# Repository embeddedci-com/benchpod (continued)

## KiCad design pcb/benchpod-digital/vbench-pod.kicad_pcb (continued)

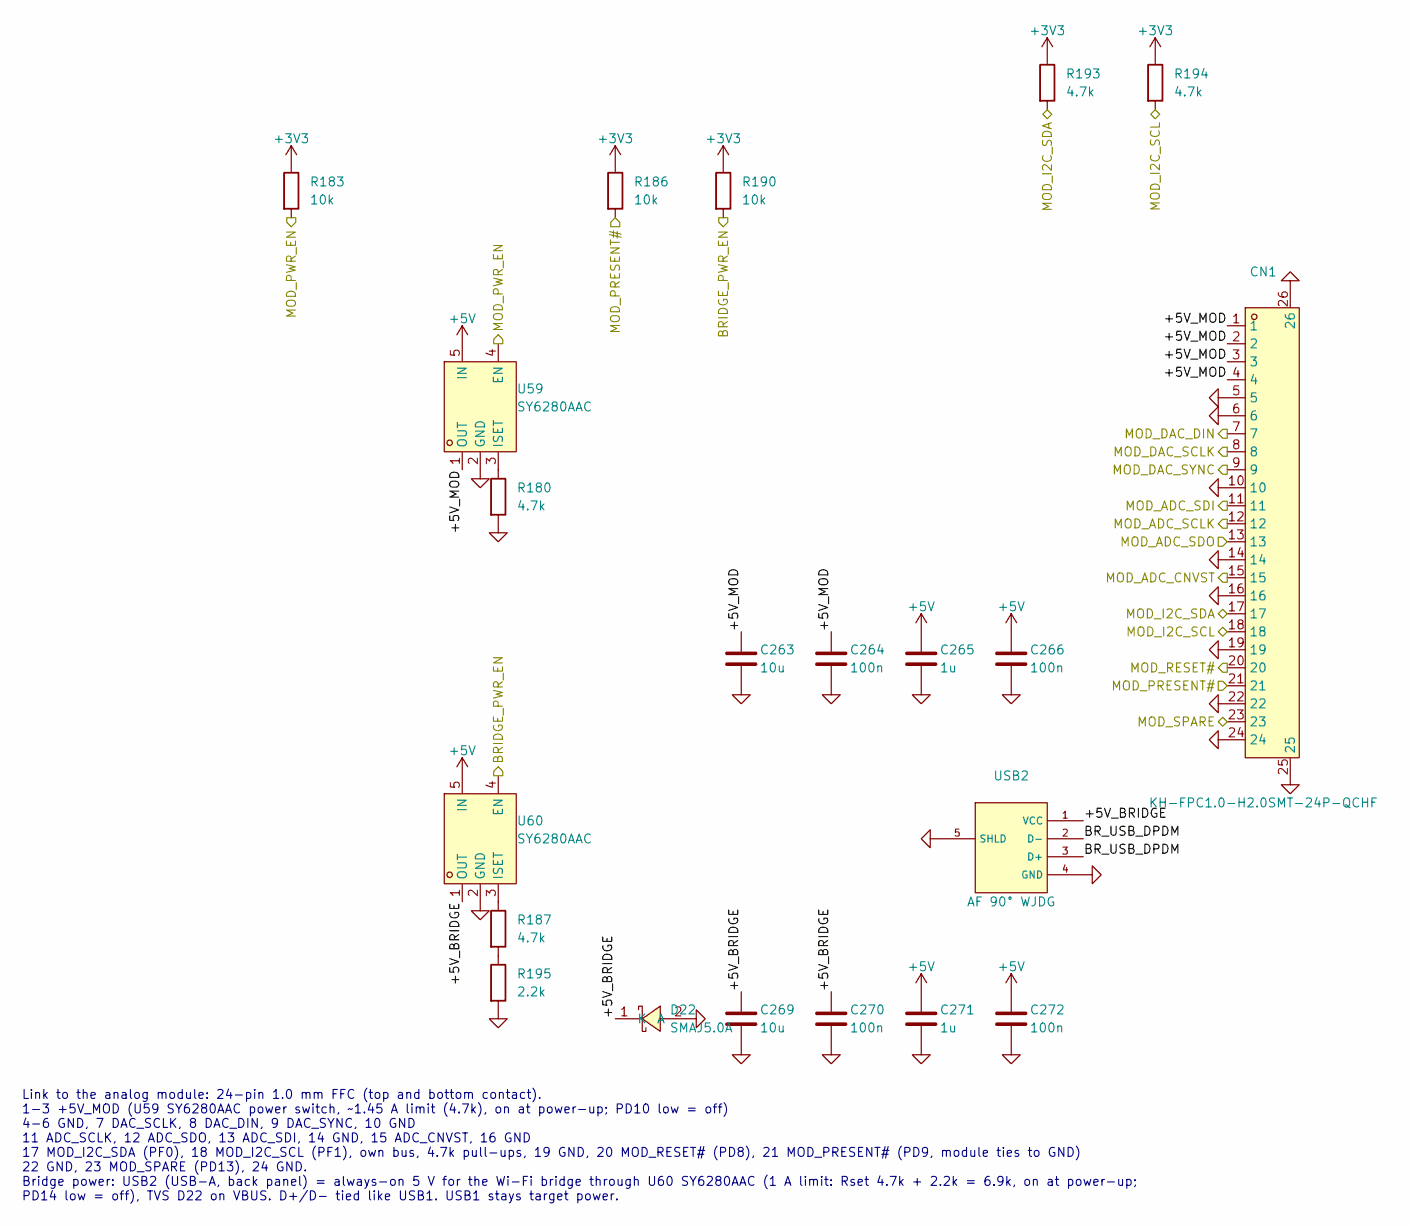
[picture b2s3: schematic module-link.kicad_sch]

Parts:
C263, C269: 10u; C_0603_1608Metric; LCSC C96446
C264, C266, C270, C272: 100n; C_0402_1005Metric; MPN CC0603KRX7R9BB104; LCSC C307331
C265, C271: 1u; C_0402_1005Metric; MPN CL05A105KA5NQNC; LCSC C52923
CN1: KH-FPC1.0-H2.0SMT-24P-QCHF; C5123103_FPC-SMD_24P-P1.00_KH-FPC1.0-H2.0SMT-24P-QCHF; LCSC C5123103
D22: SMAJ5.0A; SMA_L4.3-W2.6-LS5.0-RD; MPN SMAJ5.0A; LCSC Part C2925443
R180, R187, R193, R194: 4.7k; R_0402_1005Metric; LCSC C25900
R183, R186, R190: 10k; R_0402_1005Metric; LCSC C25744
R195: 2.2k; R_0402_1005Metric; LCSC C25879
U59, U60: SY6280AAC; C55136_SOT-23-5_L3.0-W1.7-P0.95-LS2.8-BL; LCSC C55136
USB2: AF 90° WJDG; C456018_USB-A-TH_AF-WJDG; LCSC C456018

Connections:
+3V3: R183.1, R186.1, R190.1, R193.1, R194.1; also elsewhere on the board
+5V: C265.1, C266.1, C271.1, C272.1, U59.5 (IN), U60.5 (IN); also elsewhere on the board
/BRIDGE_PWR_EN: R190.2, U60.4 (EN); also elsewhere on the board
/MOD_ADC_CNVST: CN1.15; also elsewhere on the board
/MOD_ADC_SCLK: CN1.12; also elsewhere on the board
/MOD_ADC_SDI: CN1.11; also elsewhere on the board
/MOD_ADC_SDO: CN1.13; also elsewhere on the board
/MOD_DAC_DIN: CN1.7; also elsewhere on the board
/MOD_DAC_SCLK: CN1.8; also elsewhere on the board
/MOD_DAC_SYNC: CN1.9; also elsewhere on the board
/MOD_I2C_SCL: CN1.18, R194.2; also elsewhere on the board
/MOD_I2C_SDA: CN1.17, R193.2; also elsewhere on the board
/MOD_PRESENT#: CN1.21, R186.2; also elsewhere on the board
/MOD_PWR_EN: R183.2, U59.4 (EN); also elsewhere on the board
/MOD_RESET#: CN1.20; also elsewhere on the board
/MOD_SPARE: CN1.23; also elsewhere on the board
/Module link, bridge power/+5V_BRIDGE: C269.1, C270.1, D22.1 (K), U60.1 (OUT), USB2.1 (VCC)
/Module link, bridge power/+5V_MOD: C263.1, C264.1, CN1.1, CN1.2, CN1.3, CN1.4, U59.1 (OUT)
/Module link, bridge power/BR_USB_DPDM: USB2.2 (D-), USB2.3 (D+)
GND: C263.2, C264.2, C265.2, C266.2, C269.2, C270.2, C271.2, C272.2, CN1.5, CN1.6, CN1.10, CN1.14, CN1.16, CN1.19, CN1.22, CN1.24, CN1.25, CN1.26, D22.2 (A), R180.2, R195.2, U59.2 (GND), U60.2 (GND), USB2.4 (GND), USB2.5 (SHLD); also elsewhere on the board
unnamed: R187.2, R195.1
unnamed: R180.1, U59.3 (ISET)
unnamed: R187.1, U60.3 (ISET)

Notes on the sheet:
Link to the analog module: 24-pin 1.0 mm FFC (top and bottom contact). 1-3 +5V_MOD (U59 SY6280AAC power switch, ~1.45 A limit (4.7k), on at power-up; PD10 low = off) 4-6 GND, 7 DAC_SCLK, 8 DAC_DIN, 9 DAC_SYNC, 10 GND 11 ADC_SCLK, 12 ADC_SDO, 13 ADC_SDI, 14 GND, 15 ADC_CNVST, 16 GND 17 MOD_I2C_SDA (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

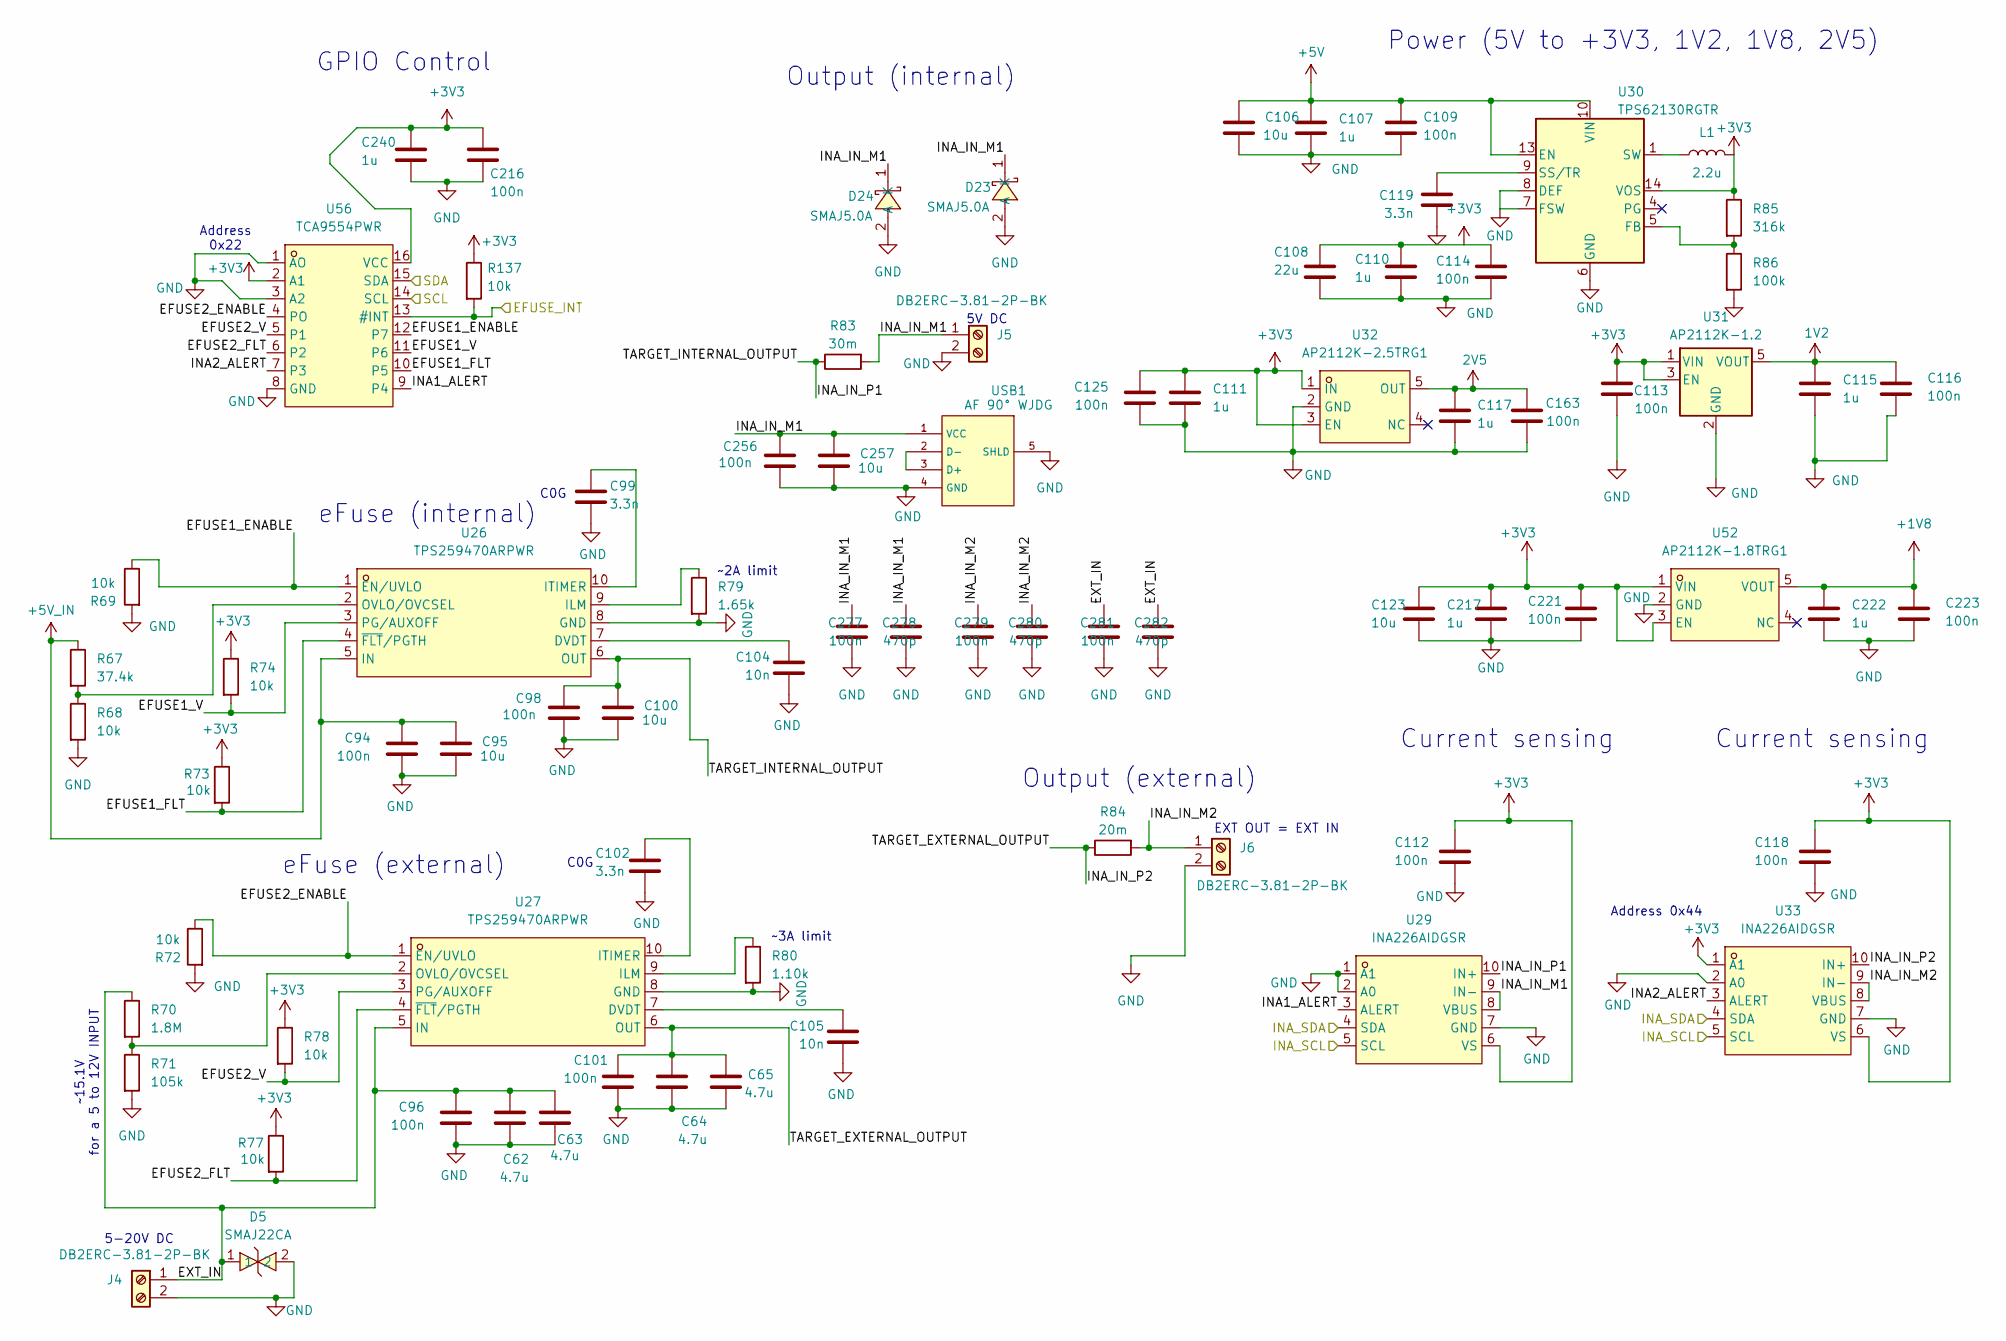
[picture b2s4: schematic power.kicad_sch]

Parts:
C62, C63, C64, C65: 4.7u; C_0805_2012Metric; LCSC C98192
C94, C96, C98, C101, C109, C112, C113, C114, C116, C118, C125, C163, C221, C223, C256, C277, C279, C281: 100n; C_0402_1005Metric; MPN CC0603KRX7R9BB104; LCSC C307331
C95, C100, C106, C257: 10u; C_0603_1608Metric; LCSC C96446
C99, C102, C119: 3.3n; C_0402_1005Metric; LCSC C26404
C104, C105: 10n; C_0402_1005Metric; LCSC C15195
C107, C110, C111, C115, C117, C217, C240: 1u; C_0402_1005Metric; MPN CL05A105KA5NQNC; LCSC C52923
C108: 22u; C_0805_2012Metric; MPN CL21B105KBFNNNE; LCSC C45783
C123: 10u; C_0603_1608Metric; MPN GRM21BR61H106KE43L; LCSC C96446
C216: 100n; C_0402_1005Metric; LCSC C307331
C222: 1u; C_0402_1005Metric; MPN GRM155R61H105KE05D; LCSC C1518208
C278, C280, C282: 470p; C_0402_1005Metric; MPN CC0603KRX7R9BB104; LCSC C1537
D5: SMAJ22CA; C41376408_SMA_L4_3-W2_6-LS5_2-RD; MPN SMAJ22CA; LCSC C5353129
D23, D24: SMAJ5.0A; SMA_L4.3-W2.6-LS5.0-RD; MPN SMAJ5.0A; LCSC Part C2925443
J4, J5, J6: DB2ERC-3.81-2P-BK; C5259145_CONN-TH_2P-P3.81_DB2ERC-3.81-2P-BK; MFR. Part # DB2ERC-3.81-2P-BK; LCSC Part # C5259145
L1: 2.2u; C167869_IND-SMD_L4.0-W4.0_FNR40XXS; LCSC C167869
R67: 37.4k; R_0402_1005Metric; LCSC C185422
R68, R69, R72, R73, R74, R77, R78, R137: 10k; R_0402_1005Metric; LCSC C25744
R70: 1.8M; R_0402_1005Metric; LCSC C38587
R71: 105k; R_0402_1005Metric; LCSC C25742
R79: 1.65k; R_0402_1005Metric; LCSC C25869
R80: 1.10k; R_0402_1005Metric; LCSC C25860
R83: 30m; R_2512_6332Metric; LCSC C2941066
R84: 20m; R_2512_6332Metric; LCSC C915979
R85: 316k; R_0402_1005Metric; LCSC C25777
R86: 100k; R_0402_1005Metric; LCSC C25741
U26, U27: TPS259470ARPWR; VQFN-10_L2.0-W2.0-P0.45-TL; MPN TPS259470ARPWR; LCSC Part C3662799
U29, U33: INA226AIDGSR; VSSOP-10_L3.0-W3.0-P0.50-LS4.9-BL; LCSC Part C49851
U30: TPS62130RGTR; C337502_VQFN-16_L3_0-W3_0-P0_50-BL-EP1_7; LCSC C43590
U31: AP2112K-1.2; SOT-25_L3.0-W1.6-P0.95-LS2.8-BR; LCSC C460310
U32: AP2112K-2.5TRG1; SOT-25-5; MPN AP2112K-2.5TRG1; LCSC Part C176945
U52: AP2112K-1.8TRG1; SOT-25_L3.0-W1.6-P0.95-LS2.8-BL; MPN AP2112K-1.8TRG1; LCSC Part C176944
U56: TCA9554PWR; TSSOP-16_L5.0-W4.4-P0.65-LS6.4-TL; MPN TCA9554PWR; LCSC Part C477924
USB1: AF 90° WJDG; C456018_USB-A-TH_AF-WJDG; LCSC C456018

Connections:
1V2: C115.2, C116.2, U31.5 (VOUT); also elsewhere on the board
2V5: C117.2, C163.2, U32.5 (OUT); also elsewhere on the board
+1V8: C222.2, C223.2, U52.5 (VOUT); also elsewhere on the board
+3V3: C108.2, C110.2, C111.2, C112.2, C113.2, C114.2, C118.2, C123.2, C125.2, C216.1, C217.2, C221.2, C240.2, L1.2, R73.1, R74.1, R77.1, R78.1, R85.1, R137.1, U29.6 (VS), U30.14 (VOS), U31.1 (VIN), U31.3 (EN), U32.1 (IN), U32.3 (EN), U33.1 (A1), U33.6 (VS), U52.1 (VIN), U52.3 (EN), U56.2 (A1), U56.16 (VCC); also elsewhere on the board
+5V: C106.2, C107.2, C109.2, U30.10 (VIN), U30.11 (VIN), U30.12 (VIN), U30.13 (EN); also elsewhere on the board
+5V_IN: C94.2, C95.1, R67.1, U26.5 (IN); also elsewhere on the board
/EFUSE_INT: R137.2, U56.13 (#INT); also elsewhere on the board
/I2C0_SCL: U29.5 (SCL), U33.5 (SCL), U56.14 (SCL); also elsewhere on the board
/I2C0_SDA: U29.4 (SDA), U33.4 (SDA), U56.15 (SDA); also elsewhere on the board
/Power/EFUSE1_ENABLE: R69.1, U26.1 (EN/UVLO), U56.12 (P7)
/Power/EFUSE1_FLT: R73.2, U26.4 (~FLT/PGTH), U56.10 (P5)
/Power/EFUSE1_V: R74.2, U26.3 (PG/AUXOFF), U56.11 (P6)
/Power/EFUSE2_ENABLE: R72.1, U27.1 (EN/UVLO), U56.4 (PO)
/Power/EFUSE2_FLT: R77.2, U27.4 (~FLT/PGTH), U56.6 (P2)
/Power/EFUSE2_V: R78.2, U27.3 (PG/AUXOFF), U56.5 (P1)
/Power/EXT_IN: C62.1, C63.1, C96.2, C281.1, C282.1, D5.1, J4.1, R70.1, U27.5 (IN)
/Power/INA1_ALERT: U29.3 (ALERT), U56.9 (P4)
/Power/INA2_ALERT: U33.3 (ALERT), U56.7 (P3)
/Power/INA_IN_M1: C256.2, C257.1, C277.1, C278.1, D23.1 (K), D24.1 (K), J5.1, R83.2, U29.8 (VBUS), U29.9 (IN-), USB1.1 (VCC)
/Power/INA_IN_M2: C279.1, C280.1, J6.1, R84.2, U33.8 (VBUS), U33.9 (IN-)
/Power/INA_IN_P1: C98.2, C100.1, R83.1, U26.6 (OUT), U29.10 (IN+)
/Power/INA_IN_P2: C64.1, C65.1, C101.2, R84.1, U27.6 (OUT), U33.10 (IN+)
GND: C62.2, C63.2, C64.2, C65.2, C94.1, C95.2, C96.1, C98.1, C99.2, C100.2, C101.1, C102.2, C104.2, C105.2, C106.1, C107.1, C108.1, C109.1, C110.1, C111.1, C112.1, C113.1, C114.1, C115.1, C116.1, C117.1, C118.1, C119.2, C123.1, C125.1, C163.1, C216.2, C217.1, C221.1, C222.1, C223.1, C240.1, C256.1, C257.2, C277.2, C278.2, C279.2, C280.2, C281.2, C282.2, D5.2, D23.2 (A), D24.2 (A), J4.2, J5.2, J6.2, R68.2, R69.2, R71.2, R72.2, R79.2, R80.2, R86.2, U26.8 (GND), U27.8 (GND), U29.1 (A1), U29.2 (A0), U29.7 (GND), U30.6 (GND), U30.7 (FSW), U30.8 (DEF), U30.15 (GND), U30.16 (GND), U30.17 (GND), U31.2 (GND), U32.2 (GND), U33.2 (A0), U33.7 (GND), U52.2 (GND), U56.1 (AO), U56.3 (A2), U56.8 (GND), USB1.4 (GND), USB1.5 (SHLD); also elsewhere on the board
unnamed: L1.1, U30.1 (SW), U30.2 (SW), U30.3 (SW)
unnamed: C104.1, U26.7 (DVDT)
unnamed: R79.1, U26.9 (ILM)
unnamed: C99.1, U26.10 (ITIMER)
unnamed: R67.2, R68.1, U26.2 (OVLO/OVCSEL)
unnamed: C105.1, U27.7 (DVDT)
unnamed: R80.1, U27.9 (ILM)
unnamed: C102.1, U27.10 (ITIMER)
unnamed: R70.2, R71.1, U27.2 (OVLO/OVCSEL)
unnamed: R85.2, R86.1, U30.5 (FB)
unnamed: C119.1, U30.9 (SS/TR)
unnamed: USB1.2 (D-), USB1.3 (D+)

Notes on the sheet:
GPIO Control
C0G
Output (internal)
~3A limit
eFuse (external)
Current sensing
5-20V DC
5V DC
~2A limit
EXT OUT = EXT IN
Address 0x44
Power (5V to +3V3, 1V2, 1V8, 2V5)
Output (external)
~15.1V for a 5 to 12V INPUT
Address 0x22
eFuse (internal)

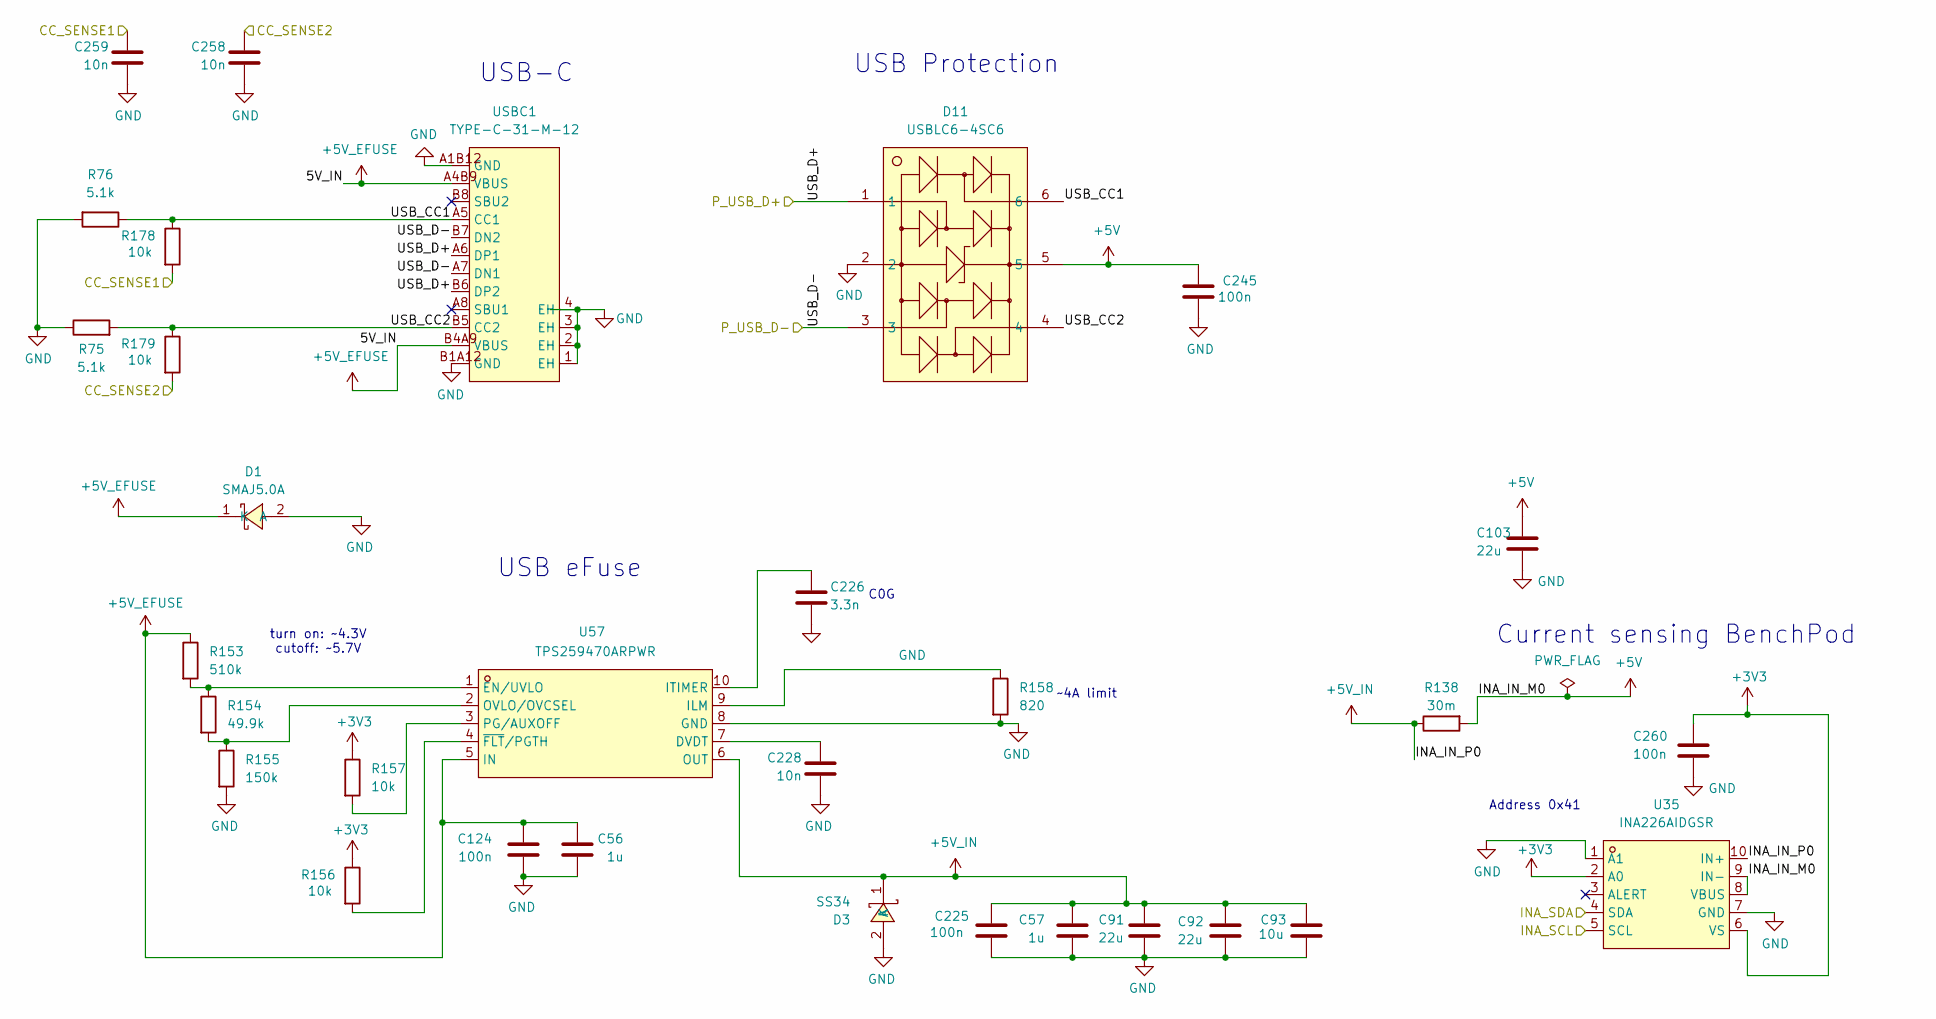
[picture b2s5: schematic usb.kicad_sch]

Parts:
C56: 1u; C_0402_1005Metric; MPN GRM155R61H105KE05D; LCSC C1518208
C57: 1u; C_0402_1005Metric; MPN CL05A105KA5NQNC; LCSC C52923
C91, C92, C103: 22u; C_0805_2012Metric; LCSC C45783
C93: 10u; C_0603_1608Metric; LCSC C96446
C124, C225, C245, C260: 100n; C_0402_1005Metric; MPN CC0603KRX7R9BB104; LCSC C307331
C226: 3.3n; C_0402_1005Metric; LCSC C26404
C228, C258, C259: 10n; C_0402_1005Metric; LCSC C15195
D1: SMAJ5.0A; SMA_L4.3-W2.6-LS5.0-RD; MPN SMAJ5.0A; LCSC Part C2925443
D3: SS34; SMA_L4.3-W2.6-LS5.2-RD; MPN SS34; LCSC Part C3014011
D11: USBLC6-4SC6; SOT-23-6_L2.9-W1.6-P0.95-LS2.8-BL; MPN USBLC6-4SC6; LCSC C111212
R75, R76: 5.1k; R_0402_1005Metric; LCSC C25905
R138: 30m; R_2512_6332Metric; LCSC C2941066
R153: 510k; R_0603_1608Metric; LCSC C23192
R154: 49.9k; R_0603_1608Metric; LCSC C23184
R155: 150k; R_0603_1608Metric; LCSC C22807
R156, R157, R178, R179: 10k; R_0402_1005Metric; LCSC C25744
R158: 820; R_0603_1608Metric; LCSC C23253
U35: INA226AIDGSR; VSSOP-10_L3.0-W3.0-P0.50-LS4.9-BL; LCSC Part C49851
U57: TPS259470ARPWR; VQFN-10_L2.0-W2.0-P0.45-TL; MPN TPS259470ARPWR; LCSC Part C3662799
USBC1: TYPE-C-31-M-12; USB-C_SMD-TYPE-C-31-M-12_1; MPN TYPE-C-31-M-12; LCSC Part C165948

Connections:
+3V3: C260.2, R156.1, R157.1, U35.2 (A0), U35.6 (VS); also elsewhere on the board
+5V: C103.1, C245.2, D11.5, R138.2, U35.8 (VBUS), U35.9 (IN-); also elsewhere on the board
+5V_EFUSE: C56.2, C124.2, D1.1 (K), R153.1, U57.5 (IN), USBC1.A4B9 (VBUS), USBC1.B4A9 (VBUS)
+5V_IN: C57.2, C91.1, C92.1, C93.1, C225.2, D3.1 (K), R138.1, U35.10 (IN+), U57.6 (OUT); also elsewhere on the board
/CC_SENSE1: C259.1, R178.2; also elsewhere on the board
/CC_SENSE2: C258.1, R179.2; also elsewhere on the board
/I2C0_SCL: U35.5 (SCL); also elsewhere on the board
/I2C0_SDA: U35.4 (SDA); also elsewhere on the board
/P_USB_D+: D11.1, USBC1.A6 (DP1), USBC1.B6 (DP2); also elsewhere on the board
/P_USB_D-: D11.3, USBC1.A7 (DN1), USBC1.B7 (DN2); also elsewhere on the board
/USB/USB_CC1: D11.6, R76.1, R178.1, USBC1.A5 (CC1)
/USB/USB_CC2: D11.4, R75.2, R179.1, USBC1.B5 (CC2)
GND: C56.1, C57.1, C91.2, C92.2, C93.2, C103.2, C124.1, C225.1, C226.2, C228.2, C245.1, C258.2, C259.2, C260.1, D1.2 (A), D3.2 (A), D11.2, R75.1, R76.2, R155.2, R158.2, U35.1 (A1), U35.7 (GND), U57.8 (GND), USBC1.1 (EH), USBC1.2 (EH), USBC1.3 (EH), USBC1.4 (EH), USBC1.A1B12 (GND), USBC1.B1A12 (GND); also elsewhere on the board
unnamed: C228.1, U57.7 (DVDT)
unnamed: R153.2, R154.1, U57.1 (EN/UVLO)
unnamed: R158.1, U57.9 (ILM)
unnamed: C226.1, U57.10 (ITIMER)
unnamed: R154.2, R155.1, U57.2 (OVLO/OVCSEL)
unnamed: R157.2, U57.3 (PG/AUXOFF)
unnamed: R156.2, U57.4 (~FLT/PGTH)

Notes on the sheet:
USB-C
Current sensing BenchPod
USB Protection
~4A limit
C0G
turn on: ~4.3V cutoff: ~5.7V
USB eFuse
Address 0x41

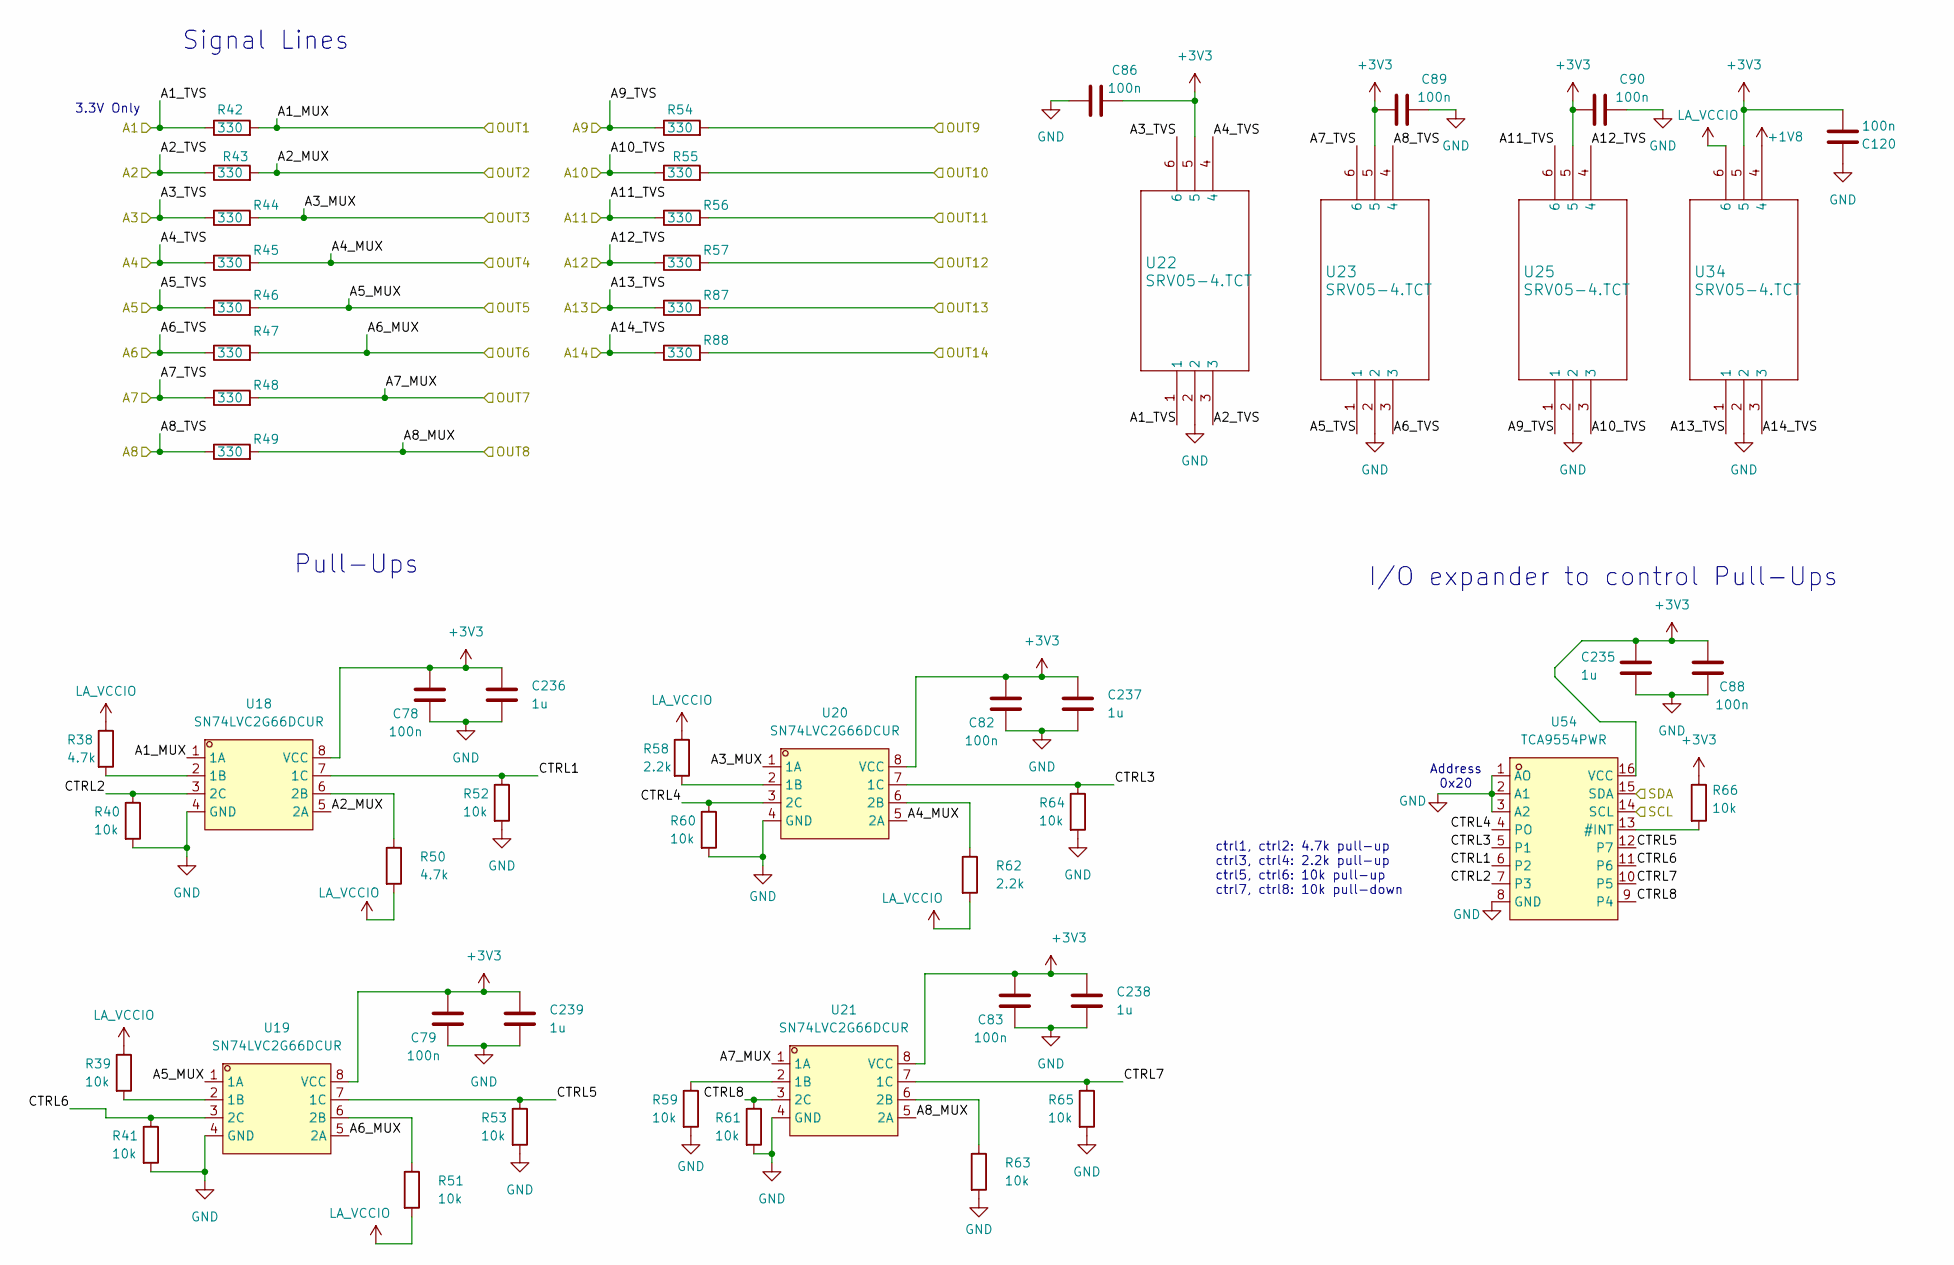
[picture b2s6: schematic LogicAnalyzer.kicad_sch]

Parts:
C78, C79, C82, C83, C86, C88, C89, C90, C120: 100n; C_0402_1005Metric; LCSC C307331
C235, C236, C237, C238, C239: 1u; C_0402_1005Metric; MPN CL05A105KA5NQNC; LCSC C52923
R38, R50: 4.7k; R_0402_1005Metric; LCSC C25900
R39, R40, R41, R51, R52, R53, R59, R60, R61, R63, R64, R65, R66: 10k; R_0402_1005Metric; LCSC C25744
R42, R43, R44, R45, R46, R47, R48, R49, R54, R55, R56, R57, R87, R88: 330; R_0402_1005Metric; LCSC C25104
R58, R62: 2.2k; R_0402_1005Metric; LCSC C25879
U18, U19, U20, U21: SN74LVC2G66DCUR; VSSOP-8_L2.1-W2.4-P0.50-LS3.2-BR; MPN SN74LVC2G66DCUR; LCSC Part C181970
U22, U23, U25, U34: SRV05-4.TCT; SOT-23-6_L2.9-W1.6-P0.95-LS2.8-BR; LCSC C13612
U54: TCA9554PWR; TSSOP-16_L5.0-W4.4-P0.65-LS6.4-TL; MPN TCA9554PWR; LCSC Part C477924

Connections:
+1V8: U34.4; also elsewhere on the board
+3V3: C78.1, C79.1, C82.1, C83.1, C86.2, C88.1, C89.1, C90.1, C120.1, C235.2, C236.2, C237.2, C238.2, C239.2, R66.1, U18.8 (VCC), U19.8 (VCC), U20.8 (VCC), U21.8 (VCC), U22.5, U23.5, U25.5, U34.5, U54.16 (VCC); also elsewhere on the board
/I2C0_SCL: U54.14 (SCL); also elsewhere on the board
/I2C0_SDA: U54.15 (SDA); also elsewhere on the board
/LA_INPUT1: R42.1, U22.1; also elsewhere on the board
/LA_INPUT2: R43.1, U22.3; also elsewhere on the board
/LA_INPUT3: R44.1, U22.6; also elsewhere on the board
/LA_INPUT4: R45.1, U22.4; also elsewhere on the board
/LA_INPUT5: R46.1, U23.1; also elsewhere on the board
/LA_INPUT6: R47.1, U23.3; also elsewhere on the board
/LA_INPUT7: R48.1, U23.6; also elsewhere on the board
/LA_INPUT8: R49.1, U23.4; also elsewhere on the board
/LA_INPUT9: R54.1, U25.1; also elsewhere on the board
/LA_INPUT10: R55.1, U25.3; also elsewhere on the board
/LA_INPUT11: R56.1, U25.6; also elsewhere on the board
/LA_INPUT12: R57.1, U25.4; also elsewhere on the board
/LA_INPUT13: R87.1, U34.1; also elsewhere on the board
/LA_INPUT14: R88.1, U34.3; also elsewhere on the board
/LA_OUT1: R42.2, U18.1 (1A); also elsewhere on the board
/LA_OUT2: R43.2, U18.5 (2A); also elsewhere on the board
/LA_OUT3: R44.2, U20.1 (1A); also elsewhere on the board
/LA_OUT4: R45.2, U20.5 (2A); also elsewhere on the board
/LA_OUT5: R46.2, U19.1 (1A); also elsewhere on the board
/LA_OUT6: R47.2, U19.5 (2A); also elsewhere on the board
/LA_OUT7: R48.2, U21.1 (1A); also elsewhere on the board
/LA_OUT8: R49.2, U21.5 (2A); also elsewhere on the board
/LA_OUT9: R54.2; also elsewhere on the board
/LA_OUT10: R55.2; also elsewhere on the board
/LA_OUT11: R56.2; also elsewhere on the board
/LA_OUT12: R57.2; also elsewhere on the board
/LA_OUT13: R87.2; also elsewhere on the board
/LA_OUT14: R88.2; also elsewhere on the board
/LogicAnalyzer/CTRL1: R52.1, U18.7 (1C), U54.6 (P2)
/LogicAnalyzer/CTRL2: R40.1, U18.3 (2C), U54.7 (P3)
/LogicAnalyzer/CTRL3: R64.1, U20.7 (1C), U54.5 (P1)
/LogicAnalyzer/CTRL4: R60.1, U20.3 (2C), U54.4 (PO)
/LogicAnalyzer/CTRL5: R53.1, U19.7 (1C), U54.12 (P7)
/LogicAnalyzer/CTRL6: R41.1, U19.3 (2C), U54.11 (P6)
/LogicAnalyzer/CTRL7: R65.1, U21.7 (1C), U54.10 (P5)
/LogicAnalyzer/CTRL8: R61.1, U21.3 (2C), U54.9 (P4)
GND: C78.2, C79.2, C82.2, C83.2, C86.1, C88.2, C89.2, C90.2, C120.2, C235.1, C236.1, C237.1, C238.1, C239.1, R40.2, R41.2, R52.2, R53.2, R59.2, R60.2, R61.2, R63.2, R64.2, R65.2, U18.4 (GND), U19.4 (GND), U20.4 (GND), U21.4 (GND), U22.2, U23.2, U25.2, U34.2, U54.1 (AO), U54.2 (A1), U54.3 (A2), U54.8 (GND); also elsewhere on the board
LA_VCCIO: R38.1, R39.1, R50.2, R51.2, R58.1, R62.2, U34.6; also elsewhere on the board
unnamed: R38.2, U18.2 (1B)
unnamed: R50.1, U18.6 (2B)
unnamed: R39.2, U19.2 (1B)
unnamed: R51.1, U19.6 (2B)
unnamed: R58.2, U20.2 (1B)
unnamed: R62.1, U20.6 (2B)
unnamed: R59.1, U21.2 (1B)
unnamed: R63.1, U21.6 (2B)
unnamed: R66.2, U54.13 (#INT)

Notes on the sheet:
ctrl1, ctrl2: 4.7k pull-up ctrl3, ctrl4: 2.2k pull-up ctrl5, ctrl6: 10k pull-up ctrl7, ctrl8: 10k pull-down
3.3V Only
I/O expander to control Pull-Ups
Signal Lines
Pull-Ups
Address 0x20

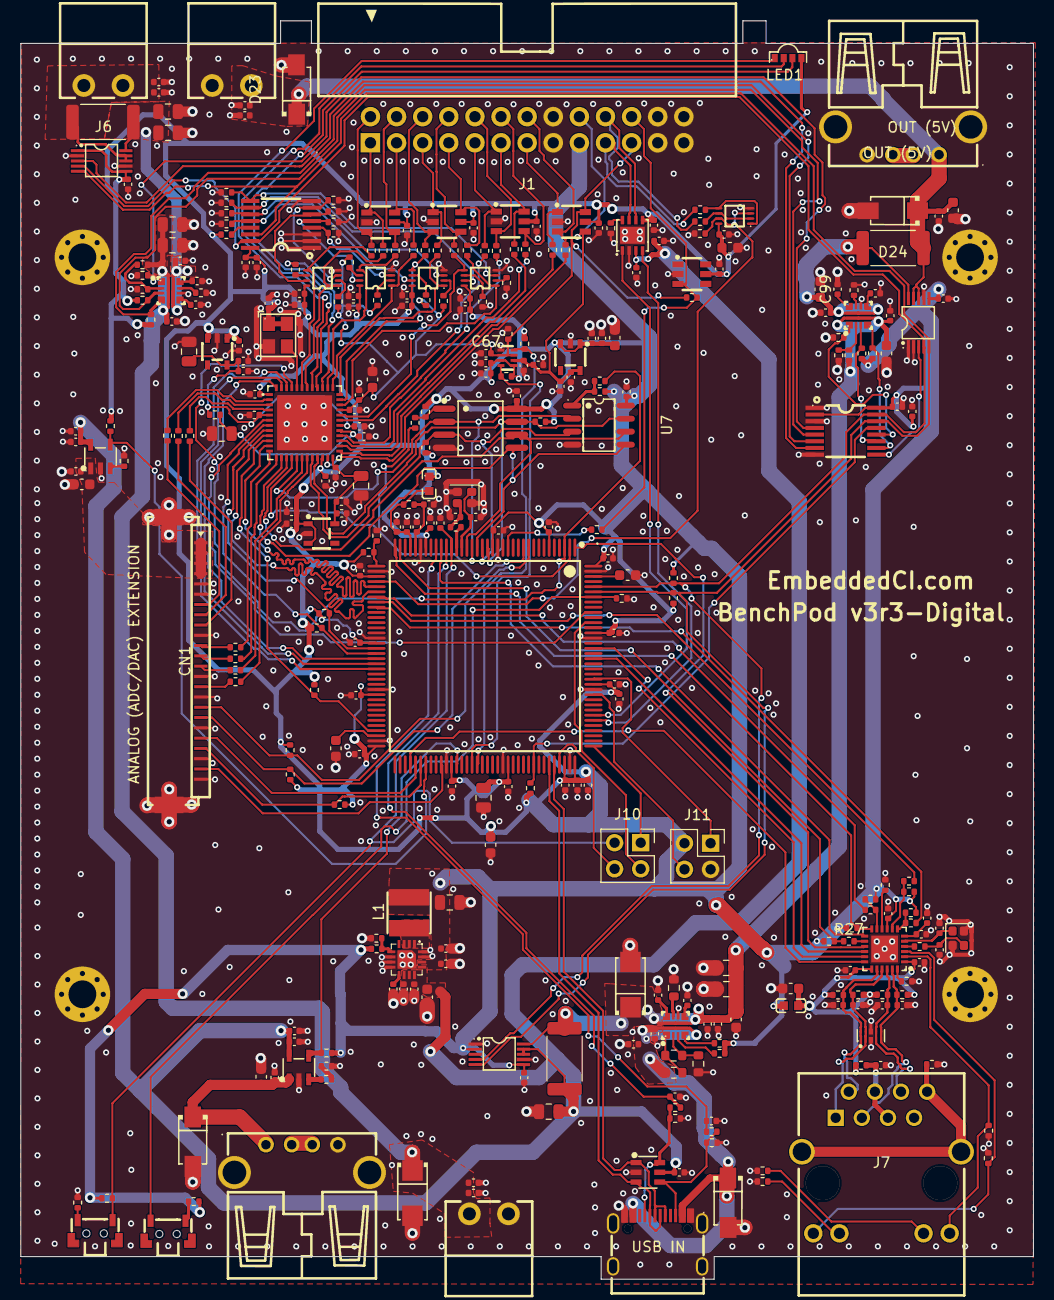
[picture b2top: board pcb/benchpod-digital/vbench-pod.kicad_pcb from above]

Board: 4 copper layers, 98.5 x 122.4 mm, 335 parts (0 on the bottom side), 205 nets.

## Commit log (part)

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2026-06-22 v2.0.0
2026-06-23 rp2350B flash fixes
